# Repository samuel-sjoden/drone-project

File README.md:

# Drone Project
**Attention**
This repository is deprecated and has since been migrated to codeberg: [link here](https://codeberg.org/drone-project)

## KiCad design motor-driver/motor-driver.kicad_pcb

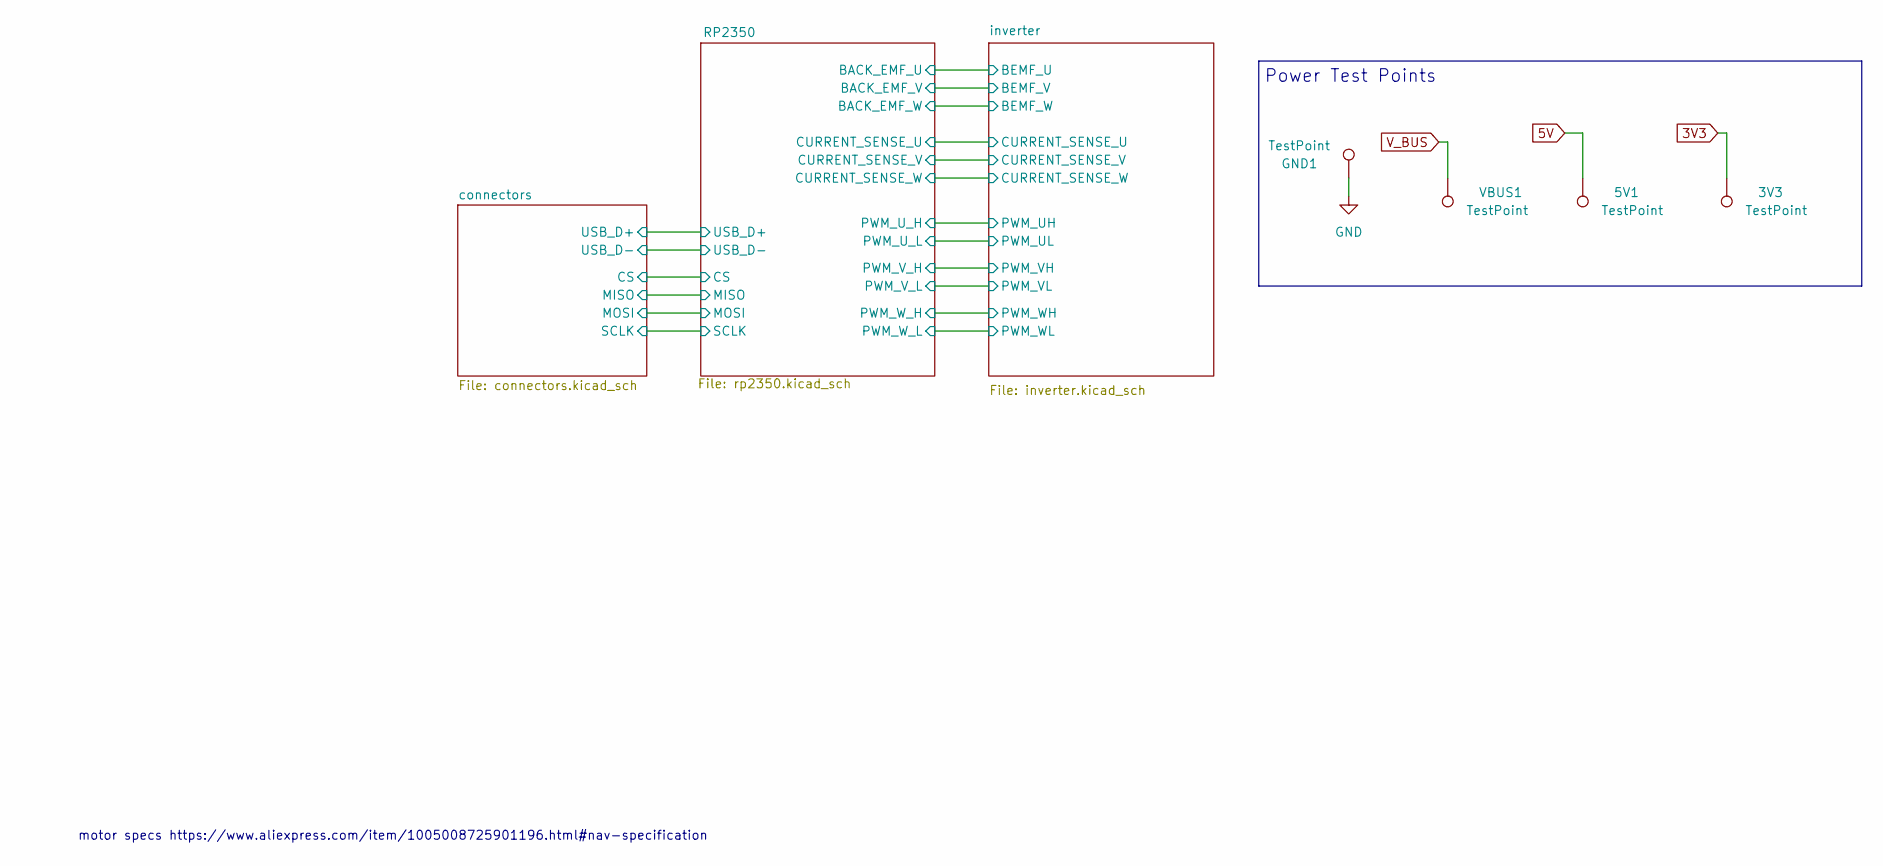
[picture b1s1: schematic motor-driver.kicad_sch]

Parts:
3V3, 5V1: TestPoint; TestPoint_THTPad_D1.0mm_Drill0.5mm
GND1: TestPoint; TestPoint_THTPad_D1.0mm_Drill0.5mm
VBUS1: TestPoint; TestPoint_THTPad_D1.0mm_Drill0.5mm

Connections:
3V3: 3V3.1; also elsewhere on the board
5V: 5V1.1; also elsewhere on the board
GND: GND1.1; also elsewhere on the board
V_BUS: VBUS1.1; also elsewhere on the board

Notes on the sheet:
motor specs https://www.aliexpress.com/item/1005008725901196.html#nav-specification
Power Test Points

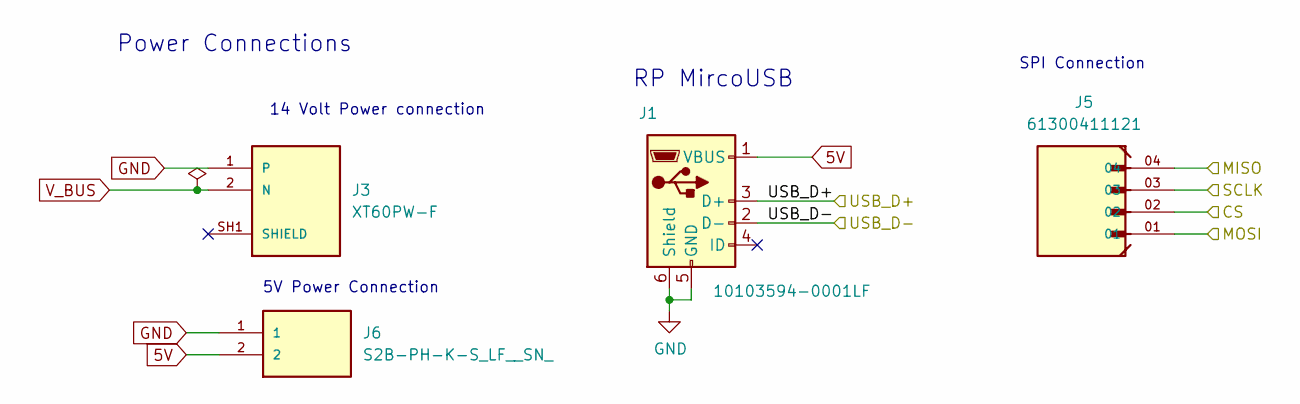
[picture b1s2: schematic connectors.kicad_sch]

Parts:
J1: 10103594-0001LF; USB_Micro-B_Amphenol_10103594-0001LF_Horizontal; MPN 10103594-0001LF
J3: XT60PW-F; AMASS_XT60PW-F; PARTREV 1.2
J5: 61300411121; WURTH_61300411121; MPN 61300411121
J6: S2B-PH-K-S_LF__SN_; JST_S2B-PH-K-S_LF__SN_

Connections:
5V: J1.1 (VBUS), J6.2; also elsewhere on the board
/RP2350/CS: J5.02; also elsewhere on the board
/RP2350/MISO: J5.04; also elsewhere on the board
/RP2350/MOSI: J5.01; also elsewhere on the board
/RP2350/SCLK: J5.03; also elsewhere on the board
/RP2350/USB_D+: J1.3 (D+); also elsewhere on the board
/RP2350/USB_D-: J1.2 (D-); also elsewhere on the board
GND: J1.5 (GND), J1.6 (Shield), J3.1, J6.1; also elsewhere on the board
V_BUS: J3.2 (N); also elsewhere on the board

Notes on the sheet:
Power Connections
14 Volt Power connection
5V Power Connection
SPI Connection
RP MircoUSB

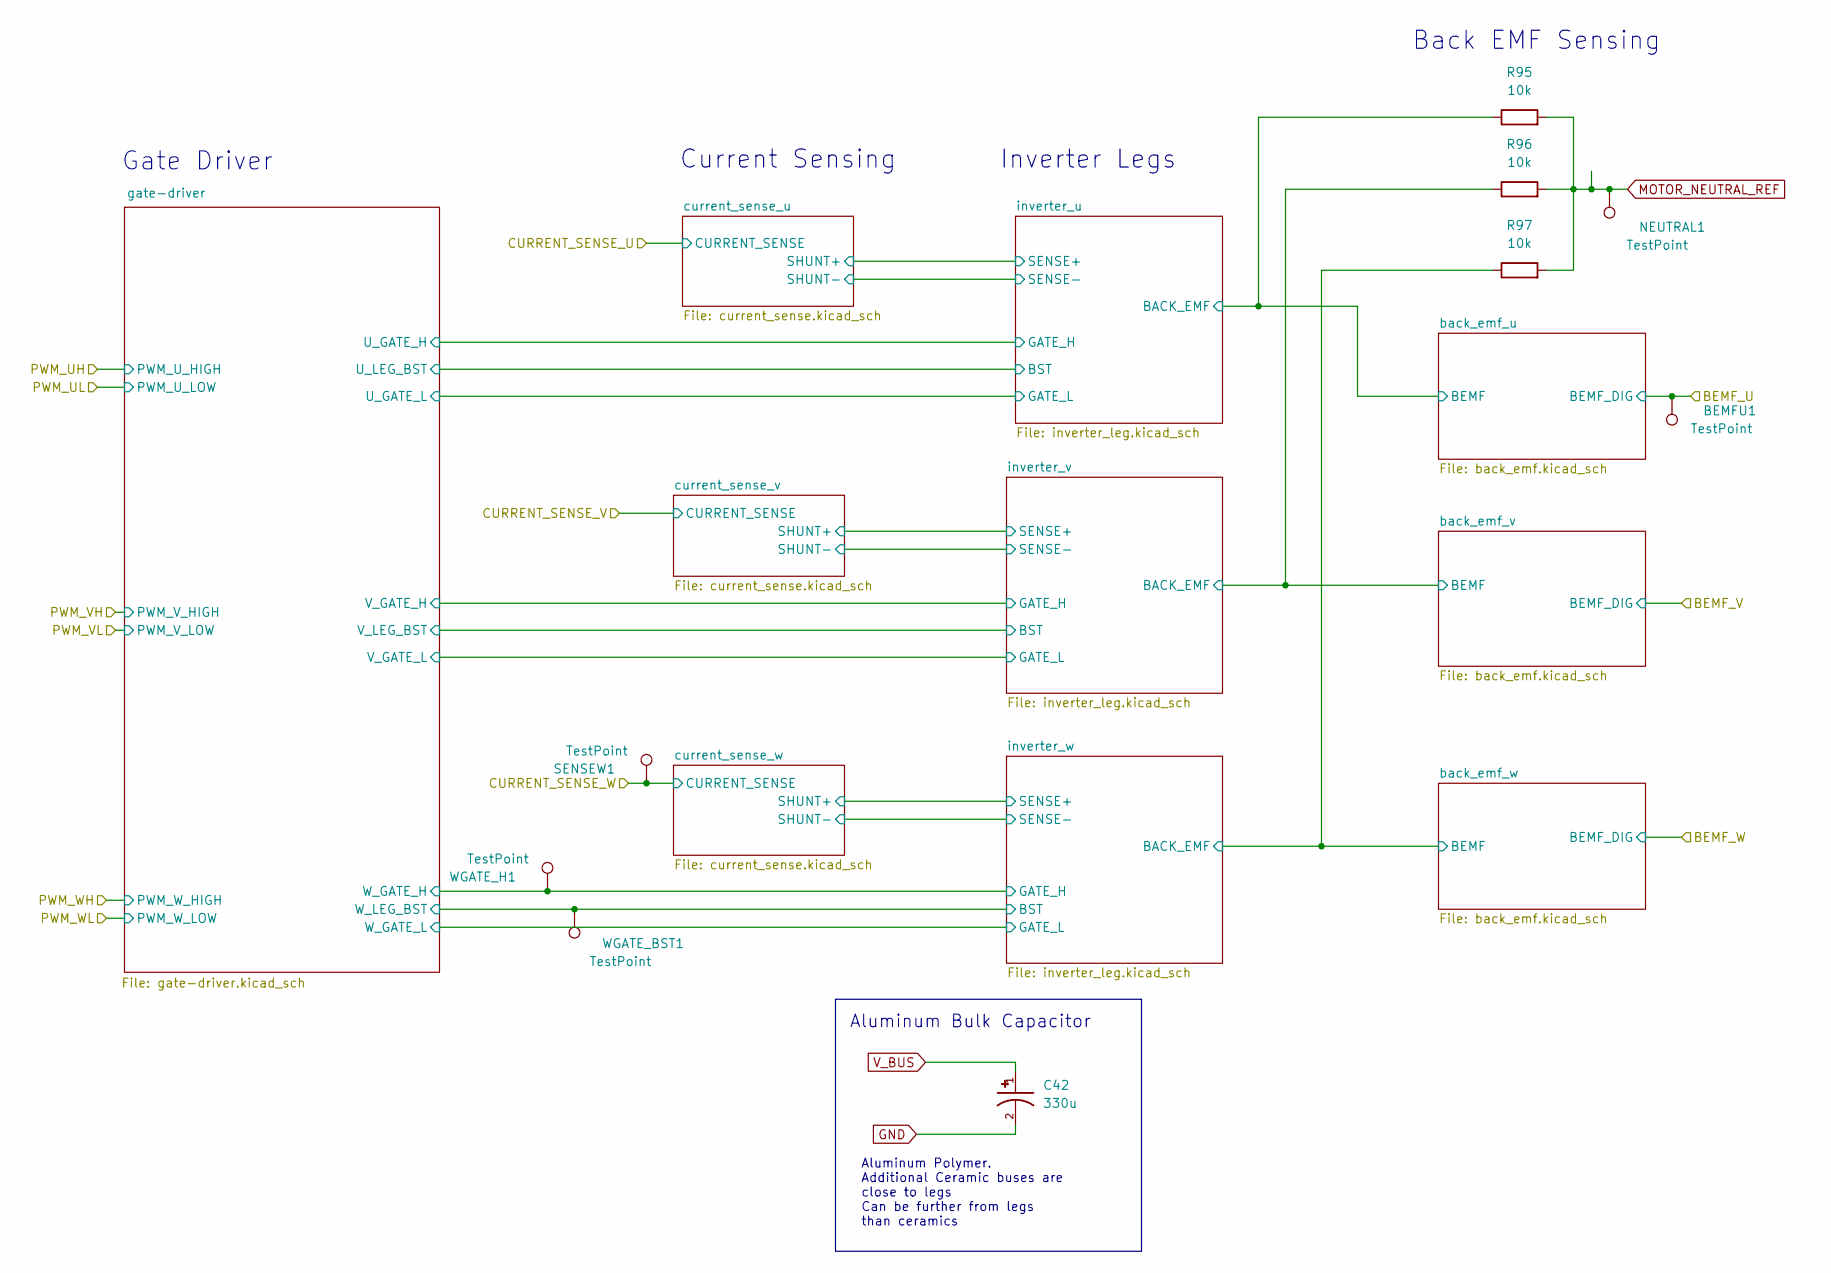
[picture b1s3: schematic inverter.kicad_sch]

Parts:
BEMFU1: TestPoint; TestPoint_THTPad_D1.0mm_Drill0.5mm
C42: 330u; CAPAE1030X1225N; PARTREV 8/5/2025
NEUTRAL1: TestPoint; TestPoint_THTPad_D1.0mm_Drill0.5mm
R95, R96, R97: 10k; R_0603_1608Metric; MPN RC0603FR-0710KL
SENSEW1: TestPoint; TestPoint_THTPad_D1.0mm_Drill0.5mm
WGATE_BST1: TestPoint; TestPoint_THTPad_D1.0mm_Drill0.5mm
WGATE_H1: TestPoint; TestPoint_THTPad_D1.0mm_Drill0.5mm

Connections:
/RP2350/BACK_EMF_U: BEMFU1.1; also elsewhere on the board
/RP2350/CURRENT_SENSE_W: SENSEW1.1; also elsewhere on the board
/inverter/gate-driver/W_GATE_H: WGATE_H1.1; also elsewhere on the board
/inverter/inverter_u/SHUNT_N: R95.1; also elsewhere on the board
/inverter/inverter_v/SHUNT_N: R96.1; also elsewhere on the board
/inverter/inverter_w/SHUNT_N: R97.1; also elsewhere on the board
/inverter/inverter_w/SHUNT_P: WGATE_BST1.1; also elsewhere on the board
GND: C42.2; also elsewhere on the board
MOTOR_NEUTRAL_REF: NEUTRAL1.1, R95.2, R96.2, R97.2; also elsewhere on the board
V_BUS: C42.1; also elsewhere on the board

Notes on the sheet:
Back EMF Sensing
Current Sensing
Gate Driver
Aluminum Bulk Capacitor
Aluminum Polymer. Additional Ceramic buses are close to legs Can be further from legs than ceramics
Inverter Legs

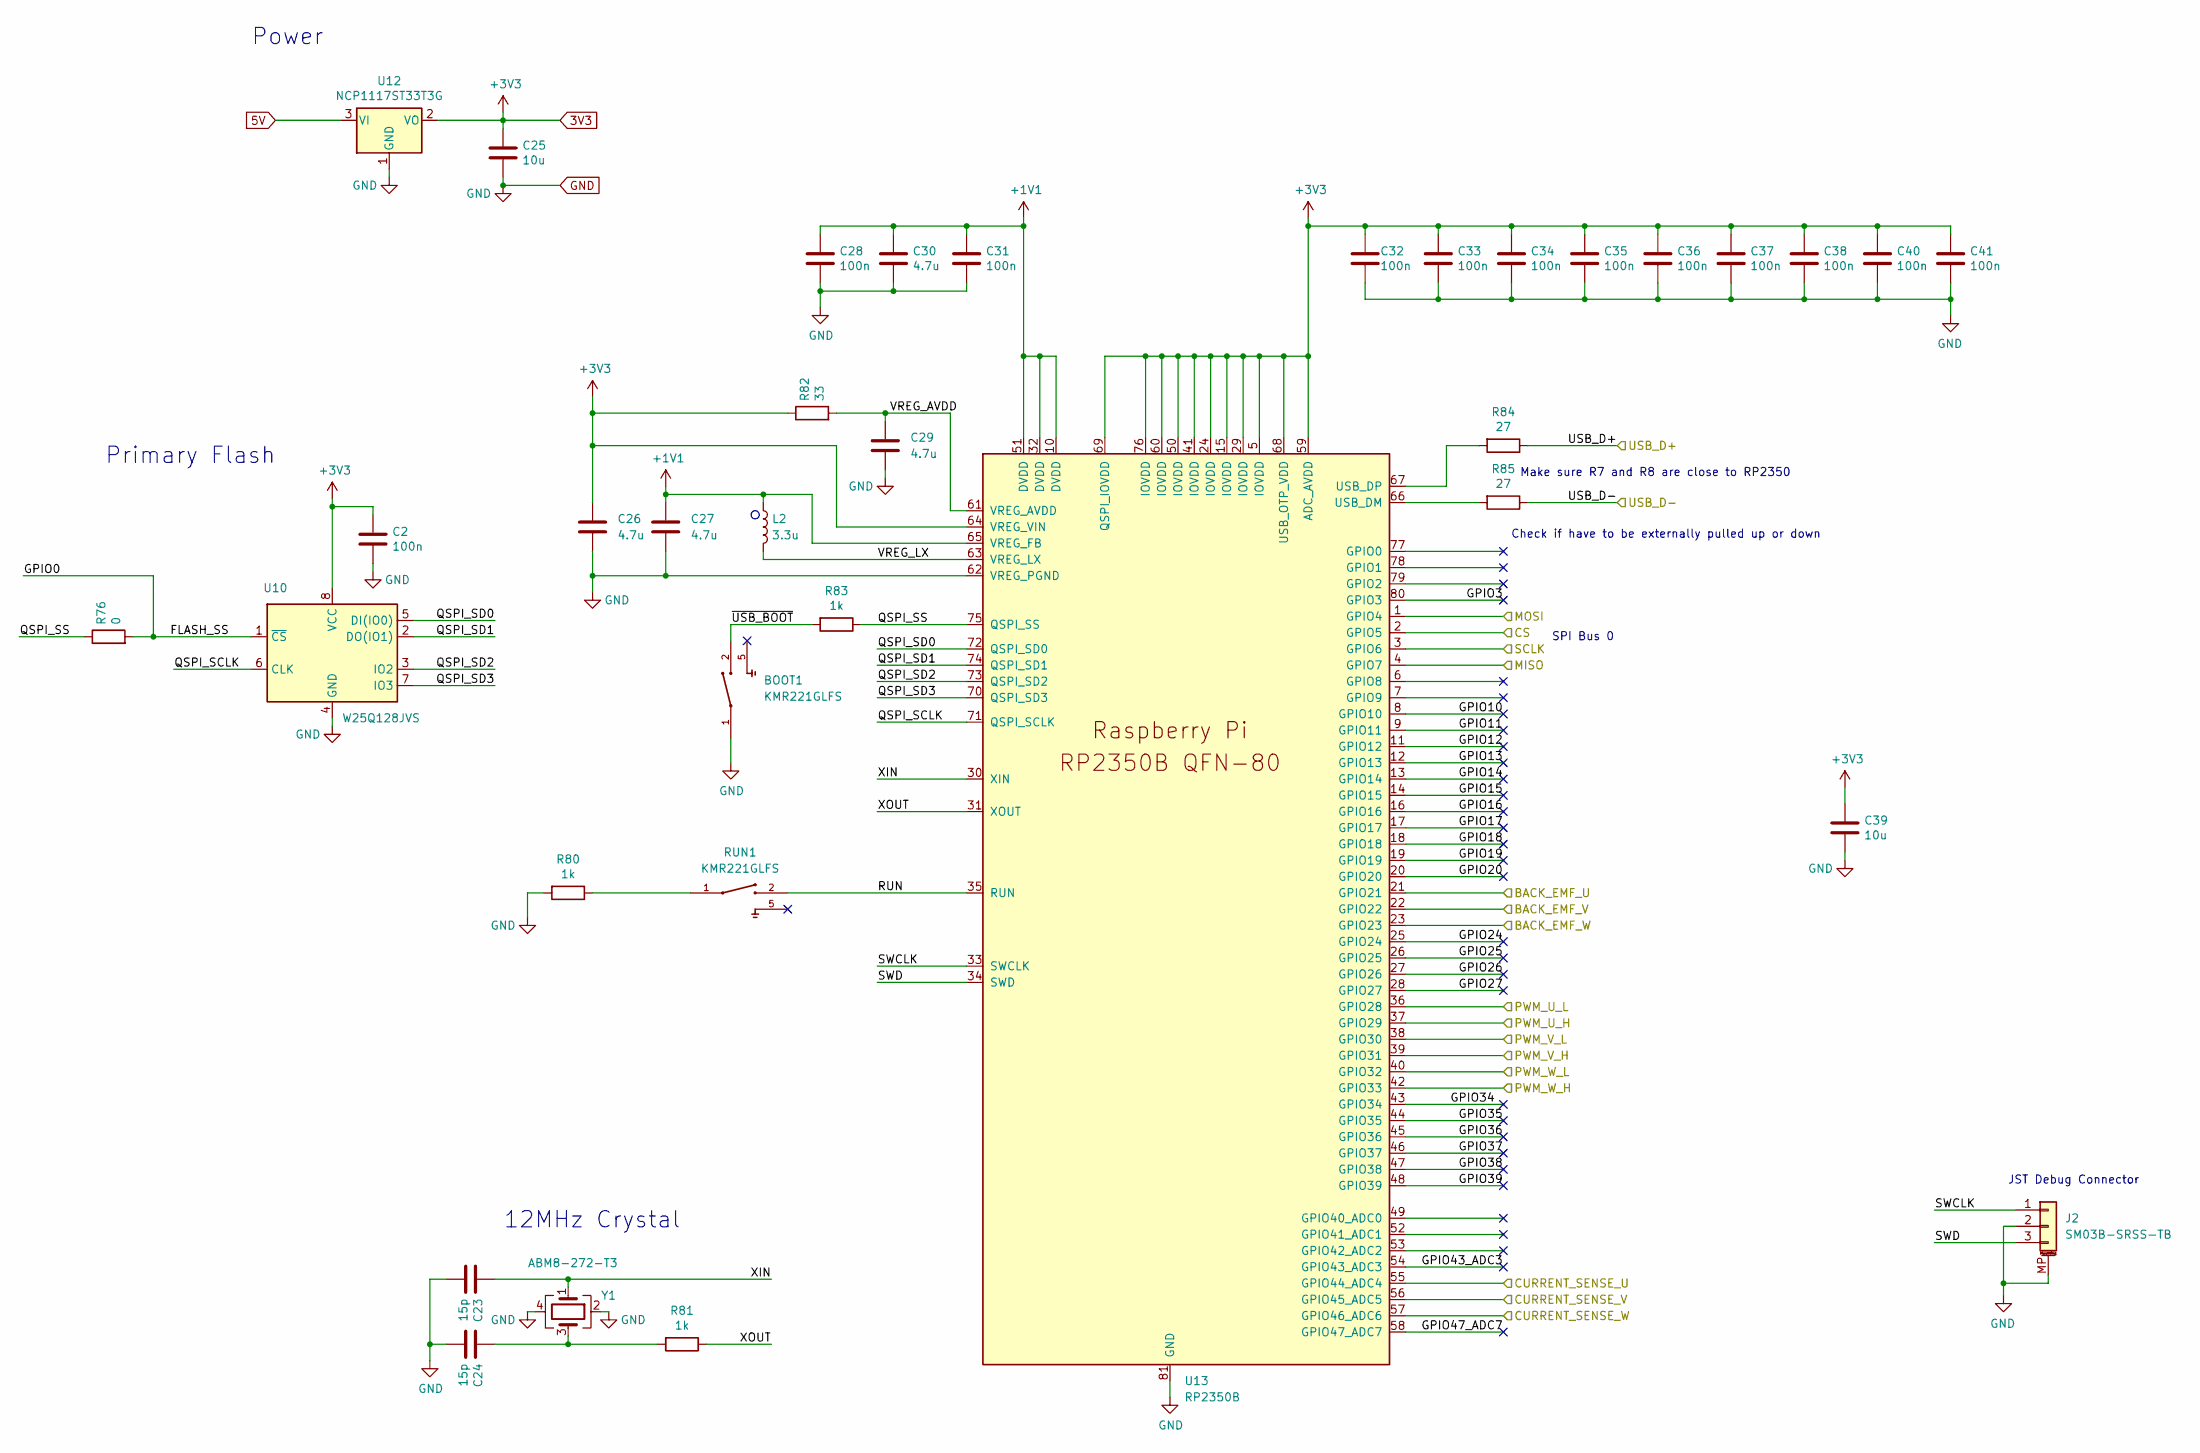
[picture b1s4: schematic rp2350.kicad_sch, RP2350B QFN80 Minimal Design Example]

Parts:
BOOT1: KMR221GLFS; SW_KMR221GLFS
C2: 100n; C_0603_1608Metric; MPN C0402C104K4RACTU
C23, C24: 15p; C_0402_1005Metric; MPN GJM1555C1H150GB01D
C25, C39: 10u; C_0603_1608Metric; MPN LMK107BBJ106MALT
C26, C27, C29, C30: 4.7u; C_0402_1005Metric; MPN CL05A475MP5NRNC
C28, C31, C32, C33, C34, C35, C36, C37, C38, C40, C41: 100n; C_0402_1005Metric; MPN C0402C104K4RACTU
J2: SM03B-SRSS-TB; JST_SH_SM03B-SRSS-TB_1x03-1MP_P1.00mm_Horizontal; MPN SM03B-SRSS-TB
L2: 3.3u; L_Cenker_CKCS201610; MPN AOTA-B201610S3R3-101-T
R76: 0; R_0603_1608Metric; MPN RC0402JR-070RL
R80, R81, R83: 1k; R_0402_1005Metric; MPN RC0402FR-071KL
R82: 33; R_0402_1005Metric; MPN RC0402JR-0733RL
R84, R85: 27; R_0402_1005Metric; MPN RC0402JR-0727RL
RUN1: KMR221GLFS; SW_KMR221GLFS
U10: W25Q128JVS; SOIC-8_5.23x5.23mm_P1.27mm
U12: NCP1117ST33T3G; SOT-223-3_TabPin2; MPN NCP1117ST33T3G
U13: RP2350B; RP2350-QFN-80-1EP_10x10_P0.4mm_EP3.4x3.4mm_ThermalVias; MPN SC1510-A4
Y1: ABM8-272-T3; Crystal_SMD_3225-4Pin_3.2x2.5mm; MPN ABM8-272-T3

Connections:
3V3: C2.1, C25.1, C26.1, C32.1, C33.1, C34.1, C35.1, C36.1, C37.1, C38.1, C39.1, C40.1, C41.1, R82.1, U10.8 (VCC), U12.2 (VO), U13.5 (IOVDD), U13.15 (IOVDD), U13.24 (IOVDD), U13.29 (IOVDD), U13.41 (IOVDD), U13.50 (IOVDD), U13.59 (ADC_AVDD), U13.60 (IOVDD), U13.64 (VREG_VIN), U13.68 (USB_OTP_VDD), U13.69 (QSPI_IOVDD), U13.76 (IOVDD); also elsewhere on the board
5V: U12.3 (VI); also elsewhere on the board
+1V1: C27.1, C28.1, C30.1, C31.1, L2.1, U13.10 (DVDD), U13.32 (DVDD), U13.51 (DVDD), U13.65 (VREG_FB)
/RP2350/BACK_EMF_U: U13.21 (GPIO21); also elsewhere on the board
/RP2350/BACK_EMF_V: U13.22 (GPIO22); also elsewhere on the board
/RP2350/BACK_EMF_W: U13.23 (GPIO23); also elsewhere on the board
/RP2350/CS: U13.2 (GPIO5); also elsewhere on the board
/RP2350/CURRENT_SENSE_U: U13.55 (GPIO44_ADC4); also elsewhere on the board
/RP2350/CURRENT_SENSE_V: U13.56 (GPIO45_ADC5); also elsewhere on the board
/RP2350/CURRENT_SENSE_W: U13.57 (GPIO46_ADC6); also elsewhere on the board
/RP2350/FLASH_SS: R76.2, U10.1 (~CS)
/RP2350/GPIO3: U13.80 (GPIO3)
/RP2350/GPIO10: U13.8 (GPIO10)
/RP2350/GPIO11: U13.9 (GPIO11)
/RP2350/GPIO12: U13.11 (GPIO12)
/RP2350/GPIO13: U13.12 (GPIO13)
/RP2350/GPIO14: U13.13 (GPIO14)
/RP2350/GPIO15: U13.14 (GPIO15)
/RP2350/GPIO16: U13.16 (GPIO16)
/RP2350/GPIO17: U13.17 (GPIO17)
/RP2350/GPIO18: U13.18 (GPIO18)
/RP2350/GPIO19: U13.19 (GPIO19)
/RP2350/GPIO20: U13.20 (GPIO20)
/RP2350/GPIO24: U13.25 (GPIO24)
/RP2350/GPIO25: U13.26 (GPIO25)
/RP2350/GPIO26: U13.27 (GPIO26)
/RP2350/GPIO27: U13.28 (GPIO27)
/RP2350/GPIO34: U13.43 (GPIO34)
/RP2350/GPIO35: U13.44 (GPIO35)
/RP2350/GPIO36: U13.45 (GPIO36)
/RP2350/GPIO37: U13.46 (GPIO37)
/RP2350/GPIO38: U13.47 (GPIO38)
/RP2350/GPIO39: U13.48 (GPIO39)
/RP2350/GPIO43_ADC3: U13.54 (GPIO43_ADC3)
/RP2350/GPIO47_ADC7: U13.58 (GPIO47_ADC7)
/RP2350/MISO: U13.4 (GPIO7); also elsewhere on the board
/RP2350/MOSI: U13.1 (GPIO4); also elsewhere on the board
/RP2350/PWM_U_H: U13.37 (GPIO29); also elsewhere on the board
/RP2350/PWM_U_L: U13.36 (GPIO28); also elsewhere on the board
/RP2350/PWM_V_H: U13.39 (GPIO31); also elsewhere on the board
/RP2350/PWM_V_L: U13.38 (GPIO30); also elsewhere on the board
/RP2350/PWM_W_H: U13.42 (GPIO33); also elsewhere on the board
/RP2350/PWM_W_L: U13.40 (GPIO32); also elsewhere on the board
/RP2350/QSPI_SCLK: U10.6 (CLK), U13.71 (QSPI_SCLK)
/RP2350/QSPI_SD0: U10.5 (DI(IO0)), U13.72 (QSPI_SD0)
/RP2350/QSPI_SD1: U10.2 (DO(IO1)), U13.74 (QSPI_SD1)
/RP2350/QSPI_SD2: U10.3 (IO2), U13.73 (QSPI_SD2)
/RP2350/QSPI_SD3: U10.7 (IO3), U13.70 (QSPI_SD3)
/RP2350/QSPI_SS: R76.1, R83.1, U13.75 (QSPI_SS)
/RP2350/RUN: RUN1.2, RUN1.3, U13.35 (RUN)
/RP2350/SCLK: U13.3 (GPIO6); also elsewhere on the board
/RP2350/SWCLK: J2.1, U13.33 (SWCLK)
/RP2350/SWD: J2.3, U13.34 (SWD)
/RP2350/USB_D+: R84.1; also elsewhere on the board
/RP2350/USB_D-: R85.1; also elsewhere on the board
/RP2350/VREG_AVDD: C29.1, R82.2, U13.61 (VREG_AVDD)
/RP2350/VREG_LX: L2.2, U13.63 (VREG_LX)
/RP2350/XIN: C23.1, U13.30 (XIN), Y1.1
/RP2350/XOUT: R81.1, U13.31 (XOUT)
/RP2350/~USB_BOOT: BOOT1.2, BOOT1.3, R83.2
GND: BOOT1.1, BOOT1.4, C2.2, C23.2, C24.2, C25.2, C26.2, C27.2, C28.2, C29.2, C30.2, C31.2, C32.2, C33.2, C34.2, C35.2, C36.2, C37.2, C38.2, C39.2, C40.2, C41.2, J2.2, J2.MP (MountPin), R80.2, U10.4 (GND), U12.1 (GND), U13.62 (VREG_PGND), U13.81 (GND), Y1.2, Y1.4; also elsewhere on the board
unnamed: C24.1, R81.2, Y1.3
unnamed: R80.1, RUN1.1, RUN1.4
unnamed: R85.2, U13.66 (USB_DM)
unnamed: R84.2, U13.67 (USB_DP)

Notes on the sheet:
12MHz Crystal
Primary Flash
Check if have to be externally pulled up or down
JST Debug Connector
Make sure R7 and R8 are close to RP2350
Power
SPI Bus 0

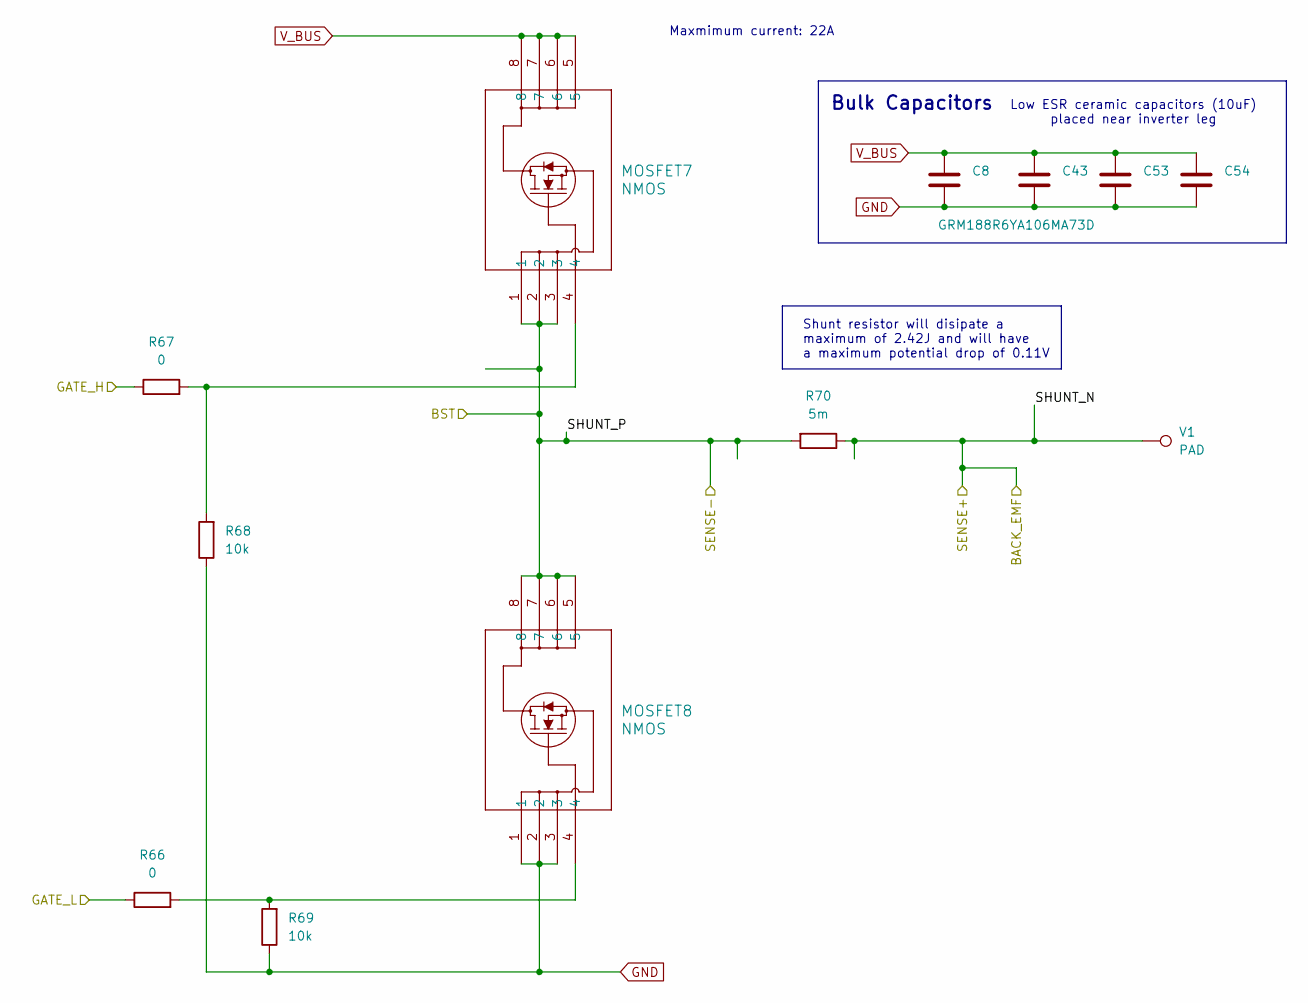
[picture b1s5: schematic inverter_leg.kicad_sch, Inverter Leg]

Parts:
C8, C43, C53, C54: GRM188R6YA106MA73D; C_0603_1608Metric; MPN GRM188R6YA106MA73D
MOSFET7, MOSFET8: NMOS; DFN5X6_8L_EP1_P_AOS; MPN AON6512
R66, R67: 0; R_0603_1608Metric; MPN RC0603FR-0722RL
R68, R69: 10k; R_0603_1608Metric; MPN RC0603FR-0710KL
R70: 5m; R_2512_6332Metric; MPN CSSU2512FT5L00
V1: PAD; TestPoint_Pad_4.0x4.0mm

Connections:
/inverter/gate-driver/V_GATE_H: R67.1; also elsewhere on the board
/inverter/gate-driver/V_GATE_L: R66.1; also elsewhere on the board
/inverter/inverter_v/SHUNT_N: R70.1, V1.1; also elsewhere on the board
/inverter/inverter_v/SHUNT_P: MOSFET7.1, MOSFET7.2, MOSFET7.3, MOSFET8.5, MOSFET8.6, MOSFET8.7, MOSFET8.8, R70.2; also elsewhere on the board
GND: C8.2, C43.2, C53.2, C54.2, MOSFET8.1, MOSFET8.2, MOSFET8.3, R68.1, R69.1; also elsewhere on the board
unnamed: MOSFET7.4, R67.2, R68.2
unnamed: MOSFET8.4, R66.2, R69.2
V_BUS: C8.1, C43.1, C53.1, C54.1, MOSFET7.5, MOSFET7.6, MOSFET7.7, MOSFET7.8; also elsewhere on the board

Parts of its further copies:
C55, C56, C57, C58, C59, C60, C61, C62: GRM188R6YA106MA73D; C_0603_1608Metric; MPN GRM188R6YA106MA73D
MOSFET1, MOSFET2, MOSFET9, MOSFET10: NMOS; DFN5X6_8L_EP1_P_AOS; MPN AON6512
R6, R27, R71, R86: 0; R_0603_1608Metric; MPN RC0603FR-0722RL
R26, R28, R87, R88: 10k; R_0603_1608Metric; MPN RC0603FR-0710KL
R29, R89: 5m; R_2512_6332Metric; MPN CSSU2512FT5L00
U1: PAD; TestPoint_Pad_4.0x4.0mm
W1: PAD; TestPoint_Pad_4.0x4.0mm

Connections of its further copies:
/inverter/gate-driver/U_GATE_H: R6.1; also elsewhere on the board
/inverter/gate-driver/U_GATE_L: R27.1; also elsewhere on the board
/inverter/gate-driver/W_GATE_H: R86.1; also elsewhere on the board
/inverter/gate-driver/W_GATE_L: R71.1; also elsewhere on the board
/inverter/inverter_u/SHUNT_N: R29.1, U1.1; also elsewhere on the board
/inverter/inverter_u/SHUNT_P: MOSFET1.1, MOSFET1.2, MOSFET1.3, MOSFET2.5, MOSFET2.6, MOSFET2.7, MOSFET2.8, R29.2; also elsewhere on the board
/inverter/inverter_w/SHUNT_N: R89.1, W1.1; also elsewhere on the board
/inverter/inverter_w/SHUNT_P: MOSFET9.1, MOSFET9.2, MOSFET9.3, MOSFET10.5, MOSFET10.6, MOSFET10.7, MOSFET10.8, R89.2; also elsewhere on the board
GND: C55.2, C56.2, C57.2, C58.2, C59.2, C60.2, C61.2, C62.2, MOSFET2.1, MOSFET2.2, MOSFET2.3, MOSFET10.1, MOSFET10.2, MOSFET10.3, R26.1, R28.1, R87.1, R88.1; also elsewhere on the board
unnamed: MOSFET1.4, R6.2, R26.2
unnamed: MOSFET2.4, R27.2, R28.2
unnamed: MOSFET9.4, R86.2, R87.2
unnamed: MOSFET10.4, R71.2, R88.2
V_BUS: C55.1, C56.1, C57.1, C58.1, C59.1, C60.1, C61.1, C62.1, MOSFET1.5, MOSFET1.6, MOSFET1.7, MOSFET1.8, MOSFET9.5, MOSFET9.6, MOSFET9.7, MOSFET9.8; also elsewhere on the board

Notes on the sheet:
Maxmimum current: 22A
Bulk Capacitors
Shunt resistor will disipate a maximum of 2.42J and will have a maximum potential drop of 0.11V
Low ESR ceramic capacitors (10uF) placed near inverter leg

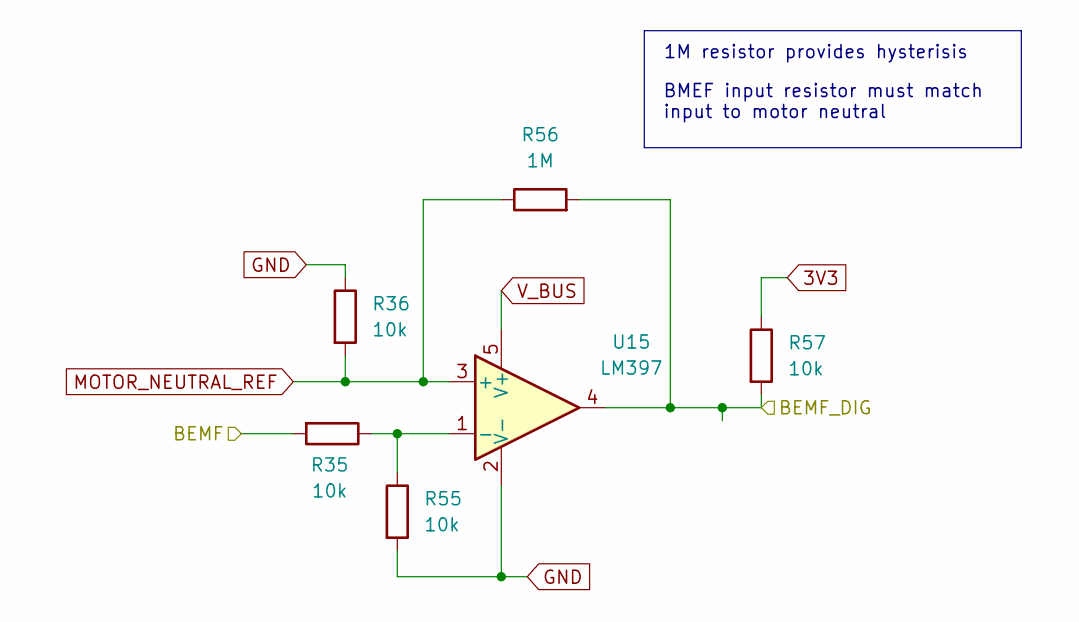
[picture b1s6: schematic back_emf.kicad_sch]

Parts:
R35, R36, R55, R57: 10k; R_0603_1608Metric; MPN RC0603FR-0710KL
R56: 1M; R_0603_1608Metric; MPN RC0603FR-071ML
U15: LM397; SOT-23-5; MPN LM397MFX/NOPB

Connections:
3V3: R57.1; also elsewhere on the board
/RP2350/BACK_EMF_V: R56.2, R57.2, U15.4; also elsewhere on the board
/inverter/inverter_v/SHUNT_N: R35.2; also elsewhere on the board
GND: R36.1, R55.2, U15.2 (V-); also elsewhere on the board
MOTOR_NEUTRAL_REF: R36.2, R56.1, U15.3 (+); also elsewhere on the board
unnamed: R35.1, R55.1, U15.1 (-)
V_BUS: U15.5 (V+); also elsewhere on the board

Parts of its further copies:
R30, R31, R32, R34, R90, R91, R92, R94: 10k; R_0603_1608Metric; MPN RC0603FR-0710KL
R33, R93: 1M; R_0603_1608Metric; MPN RC0603FR-071ML
U14, U16: LM397; SOT-23-5; MPN LM397MFX/NOPB

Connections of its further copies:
3V3: R34.1, R94.1; also elsewhere on the board
/RP2350/BACK_EMF_U: R33.2, R34.2, U14.4; also elsewhere on the board
/RP2350/BACK_EMF_W: R93.2, R94.2, U16.4; also elsewhere on the board
/inverter/inverter_u/SHUNT_N: R30.2; also elsewhere on the board
/inverter/inverter_w/SHUNT_N: R90.2; also elsewhere on the board
GND: R31.1, R32.2, R91.1, R92.2, U14.2 (V-), U16.2 (V-); also elsewhere on the board
MOTOR_NEUTRAL_REF: R31.2, R33.1, R91.2, R93.1, U14.3 (+), U16.3 (+); also elsewhere on the board
unnamed: R30.1, R32.1, U14.1 (-)
unnamed: R90.1, R92.1, U16.1 (-)
V_BUS: U14.5 (V+), U16.5 (V+); also elsewhere on the board

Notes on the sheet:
1M resistor provides hysterisis
BMEF input resistor must match input to motor neutral

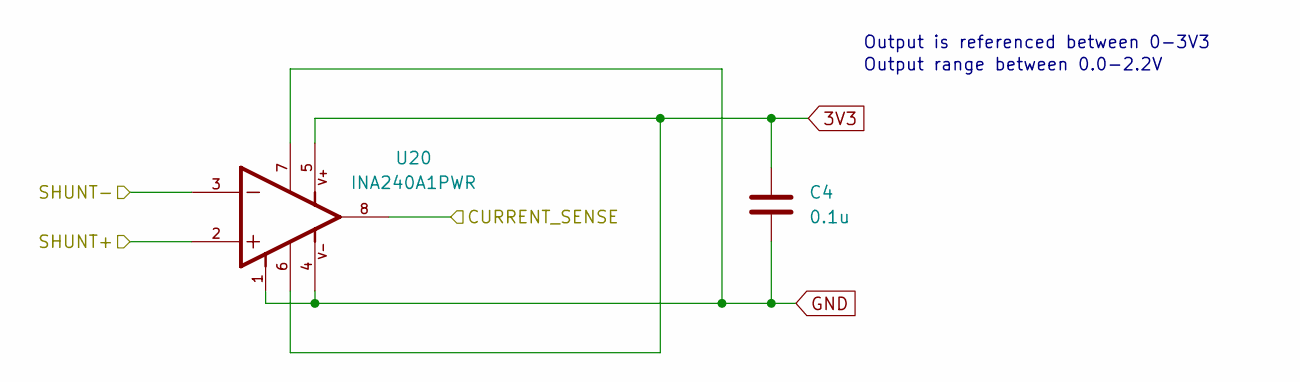
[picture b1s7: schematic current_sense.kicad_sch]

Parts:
C4: 0.1u; C_0603_1608Metric; MPN C0603C104K5RACTU
U20: INA240A1PWR; SOP65P640X120-8N; PARTREV C

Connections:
3V3: C4.1, U20.5, U20.6; also elsewhere on the board
/RP2350/CURRENT_SENSE_V: U20.8; also elsewhere on the board
/inverter/inverter_v/SHUNT_N: U20.2; also elsewhere on the board
/inverter/inverter_v/SHUNT_P: U20.3; also elsewhere on the board
GND: C4.2, U20.1, U20.4, U20.7; also elsewhere on the board

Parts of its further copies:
C3, C5: 0.1u; C_0603_1608Metric; MPN C0603C104K5RACTU
U19, U21: INA240A1PWR; SOP65P640X120-8N; PARTREV C

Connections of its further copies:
3V3: C3.1, C5.1, U19.5, U19.6, U21.5, U21.6; also elsewhere on the board
/RP2350/CURRENT_SENSE_U: U19.8; also elsewhere on the board
/RP2350/CURRENT_SENSE_W: U21.8; also elsewhere on the board
/inverter/inverter_u/SHUNT_N: U19.2; also elsewhere on the board
/inverter/inverter_u/SHUNT_P: U19.3; also elsewhere on the board
/inverter/inverter_w/SHUNT_N: U21.2; also elsewhere on the board
/inverter/inverter_w/SHUNT_P: U21.3; also elsewhere on the board
GND: C3.2, C5.2, U19.1, U19.4, U19.7, U21.1, U21.4, U21.7; also elsewhere on the board

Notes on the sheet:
Output is referenced between 0-3V3
Output range between 0.0-2.2V

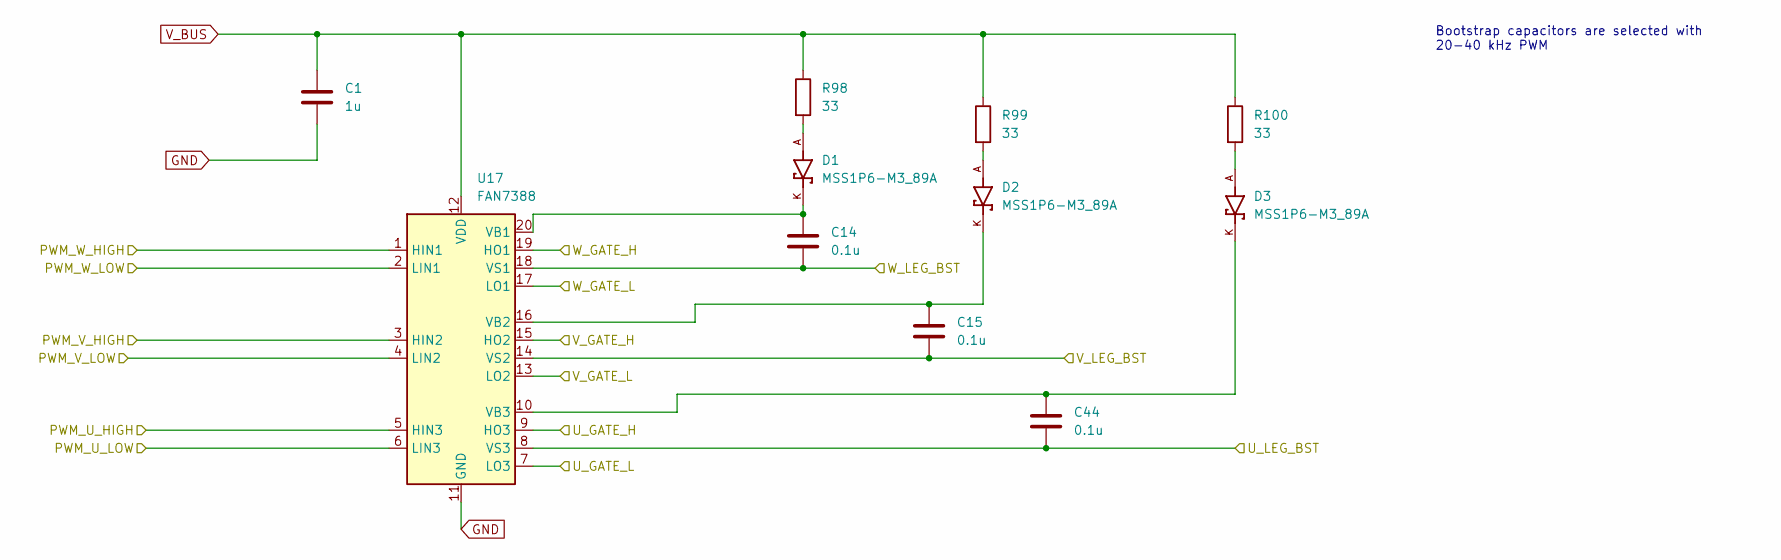
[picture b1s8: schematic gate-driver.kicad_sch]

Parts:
C1: 1u; C_0603_1608Metric; MPN C0603C105K4RACTU
C14, C15, C44: 0.1u; C_0603_1608Metric; MPN C0603C104K5RACTU
D1, D2, D3: MSS1P6-M3_89A; DIO_MSS1P6-M3_89A; PARTREV 03-Aug-2020
R98, R99, R100: 33; R_0603_1608Metric; MPN RC0603FR-0733RL
U17: FAN7388; SOIC-20W_7.5x12.8mm_P1.27mm; MPN FAN7388MX

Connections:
/RP2350/PWM_U_H: U17.5 (HIN3); also elsewhere on the board
/RP2350/PWM_U_L: U17.6 (LIN3); also elsewhere on the board
/RP2350/PWM_V_H: U17.3 (HIN2); also elsewhere on the board
/RP2350/PWM_V_L: U17.4 (LIN2); also elsewhere on the board
/RP2350/PWM_W_H: U17.1 (HIN1); also elsewhere on the board
/RP2350/PWM_W_L: U17.2 (LIN1); also elsewhere on the board
/inverter/gate-driver/U_GATE_H: U17.9 (HO3); also elsewhere on the board
/inverter/gate-driver/U_GATE_L: U17.7 (LO3); also elsewhere on the board
/inverter/gate-driver/V_GATE_H: U17.15 (HO2); also elsewhere on the board
/inverter/gate-driver/V_GATE_L: U17.13 (LO2); also elsewhere on the board
/inverter/gate-driver/W_GATE_H: U17.19 (HO1); also elsewhere on the board
/inverter/gate-driver/W_GATE_L: U17.17 (LO1); also elsewhere on the board
/inverter/inverter_u/SHUNT_P: C44.1, U17.8 (VS3); also elsewhere on the board
/inverter/inverter_v/SHUNT_P: C15.1, U17.14 (VS2); also elsewhere on the board
/inverter/inverter_w/SHUNT_P: C14.1, U17.18 (VS1); also elsewhere on the board
GND: C1.2, U17.11 (GND); also elsewhere on the board
unnamed: D1.A, R98.2
unnamed: D2.A, R99.2
unnamed: D3.A, R100.2
unnamed: C14.2, D1.K, U17.20 (VB1)
unnamed: C15.2, D2.K, U17.16 (VB2)
unnamed: C44.2, D3.K, U17.10 (VB3)
V_BUS: C1.1, R98.1, R99.1, R100.1, U17.12 (VDD); also elsewhere on the board

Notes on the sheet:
Bootstrap capacitors are selected with 20-40 kHz PWM
